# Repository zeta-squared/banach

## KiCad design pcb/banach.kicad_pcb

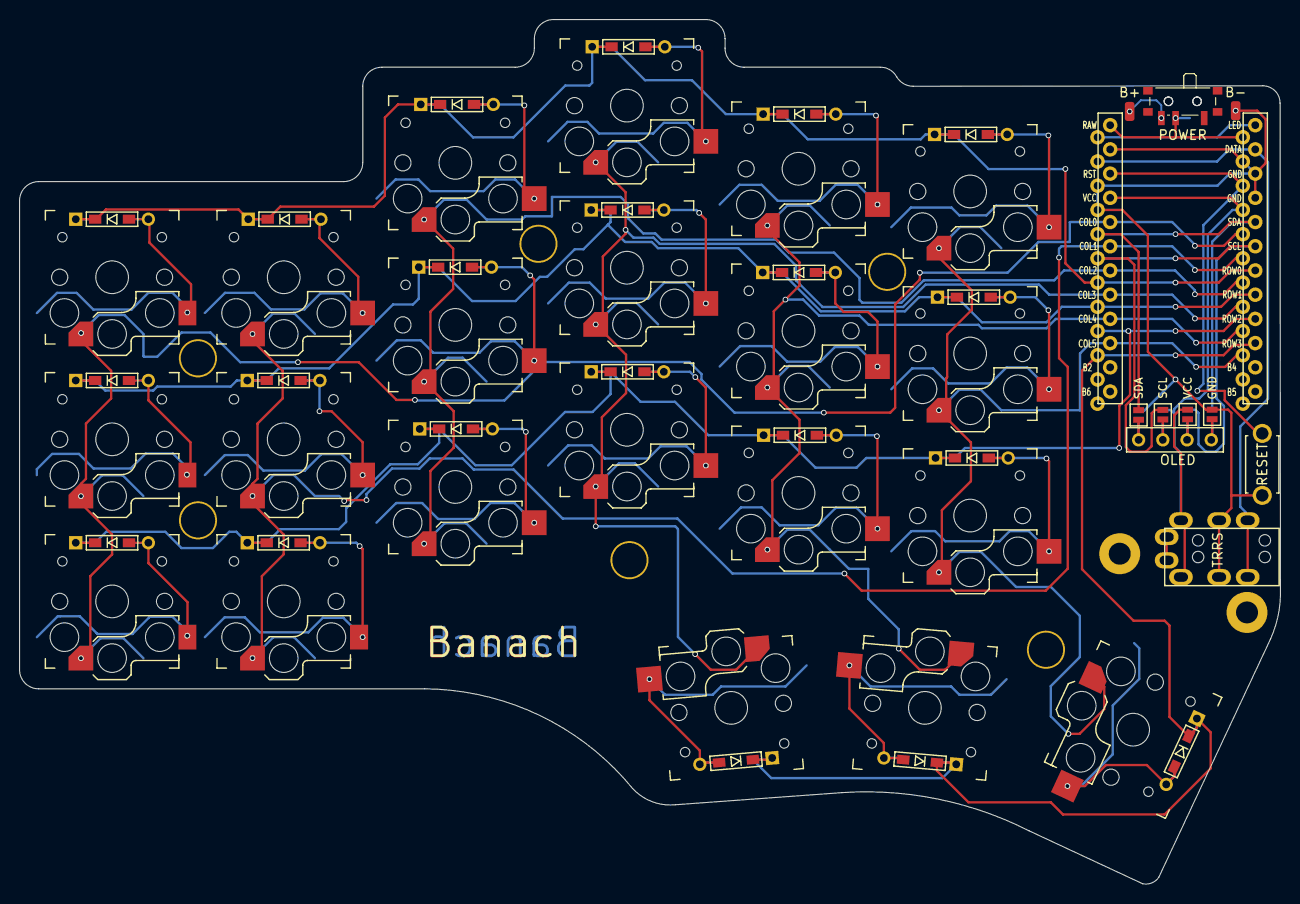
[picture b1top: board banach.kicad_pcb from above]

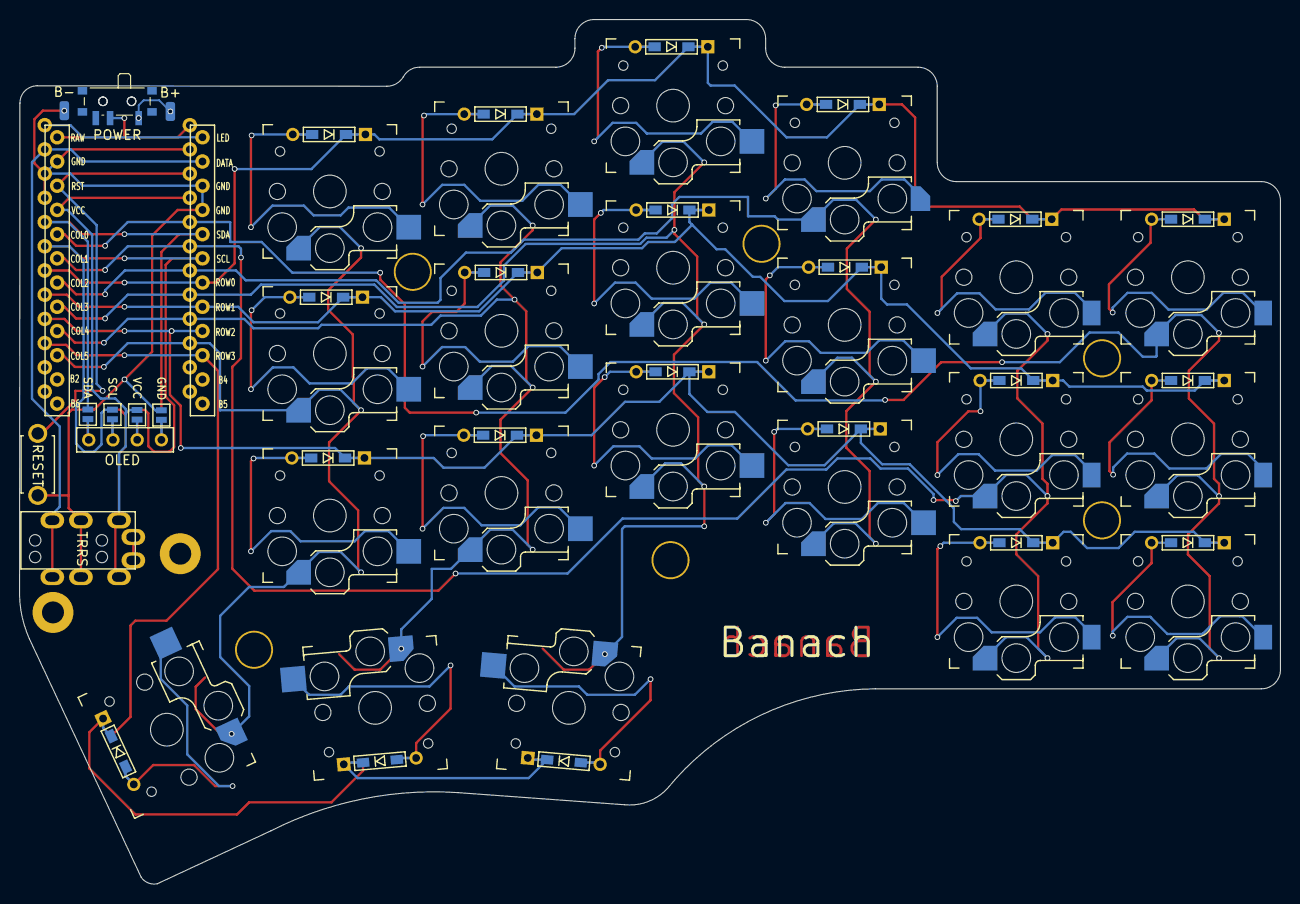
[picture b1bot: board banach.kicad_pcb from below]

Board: 2 copper layers, 132.3 x 90.7 mm, 68 parts (7 on the bottom side), 43 nets.

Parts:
B+: B+; SolderWirePad_1x01_SMD_1x2mm
B+#2: B+; SolderWirePad_1x01_SMD_1x2mm
B-: B-; SolderWirePad_1x01_SMD_1x2mm
B-#2: B-; SolderWirePad_1x01_SMD_1x2mm
D2, D2#2, D3, D4, D5, D6, D8, D8#2, D9, D10, D11, D12, D14, D14#2, D15, D16, D17, D18, D19, D20, D21: D; D3_TH_SMD
J1: MJ-4PP-9
J2: OLED
JP6, JP61: SDA; Jumper
JP62, JP68: GND; Jumper
JP63, JP66: SCL; Jumper
JP64, JP65: VCC; Jumper
POWER: SW_SPDT_PCM12
POWER#2: SW_SPDT_PCM12
RSW1: Val**; ResetSW
SW2, SW2#2, SW3, SW4, SW5, SW6, SW8, SW8#2, SW9, SW10, SW11, SW12, SW14, SW14#2, SW15, SW16, SW17, SW18, SW19, SW20, SW21: SW_PUSH; Kailh_socket_PG1350_reversible
U1: ProMicro; ProMicro_v2
h1: h1; LEGO_HOLE
h2: h2; LEGO_HOLE
h3: h3; LEGO_HOLE
h4: h4; LEGO_HOLE
h5: h5; LEGO_HOLE
h6: h6; LEGO_HOLE
h7: h7; LEGO_HOLE
h8: h8; LEGO_HOLE

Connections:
Batt+: B+.1, B+#2.1, POWER.3, POWER#2.1
GND: B-.1, B-#2.1, J1.C, JP62.1, JP68.1, RSW1.1, U1.3, U1.4, U1.23
unnamed: D2#2.2, SW2#2.2
unnamed: D2.2, SW2.2
unnamed: D3.2, SW3.2
unnamed: D4.2, SW4.2
unnamed: D5.2, SW5.2
unnamed: D6.2, SW6.2
unnamed: D8#2.2, SW8#2.2
unnamed: D8.2, SW8.2
unnamed: D9.2, SW9.2
unnamed: D10.2, SW10.2
unnamed: D11.2, SW11.2
unnamed: D12.2, SW12.2
unnamed: D14#2.2, SW14#2.2
unnamed: D14.2, SW14.2
unnamed: D15.2, SW15.2
unnamed: D16.2, SW16.2
unnamed: D17.2, SW17.2
unnamed: D18.2, SW18.2
unnamed: D19.2, SW19.2
unnamed: D20.2, SW20.2
unnamed: D21.2, SW21.2
unnamed: J2.3, JP65.2, JP66.2
unnamed: J2.4, JP6.2, JP68.2
unnamed: J2.2, JP63.2, JP64.2
unnamed: J2.1, JP61.2, JP62.2
RAW: POWER.2, POWER#2.2, U1.24
SCL: JP63.1, JP66.1, U1.6
SDA: JP6.1, JP61.1, U1.5
VCC: J1.D, JP64.1, JP65.1, U1.21
col0: SW2#2.1, SW8#2.1, SW14#2.1, U1.20
col1: SW2.1, SW8.1, SW14.1, U1.19
col2: SW3.1, SW9.1, SW15.1, U1.18
col3: SW4.1, SW10.1, SW16.1, SW19.1, U1.17
col4: SW5.1, SW11.1, SW17.1, SW20.1, U1.16
col5: SW6.1, SW12.1, SW18.1, SW21.1, U1.15
data: J1.B, U1.2
reset: RSW1.2, U1.22
row0: D2.1, D2#2.1, D3.1, D4.1, D5.1, D6.1, U1.7
row1: D8.1, D8#2.1, D9.1, D10.1, D11.1, D12.1, U1.8
row2: D14.1, D14#2.1, D15.1, D16.1, D17.1, D18.1, U1.9
row3: D19.1, D20.1, D21.1, U1.10

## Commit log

2022-10-25 rotated battery pads 90 degrees
2022-10-26 Moved power switch to top of the board where the USB port will be located. Increased through hole diameter for screws and standoffs. Completed top and bottom plates. Attempting to make version for 5p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
2022-10-27 aligned column 0 to true choc spacing
